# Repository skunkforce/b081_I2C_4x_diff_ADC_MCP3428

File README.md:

# edgy_board number b081
This design is part of the [edgy board project](https://github.com/skunkforce/edgy_boards).

# getting started
This repository uses submodules. After cloning use the command 

```$ git submodule update --init --recursive```

to pull the submodules before opening the project with kicad. 

# Tests
Tests can be found in [TESTS.md](TESTS.md)

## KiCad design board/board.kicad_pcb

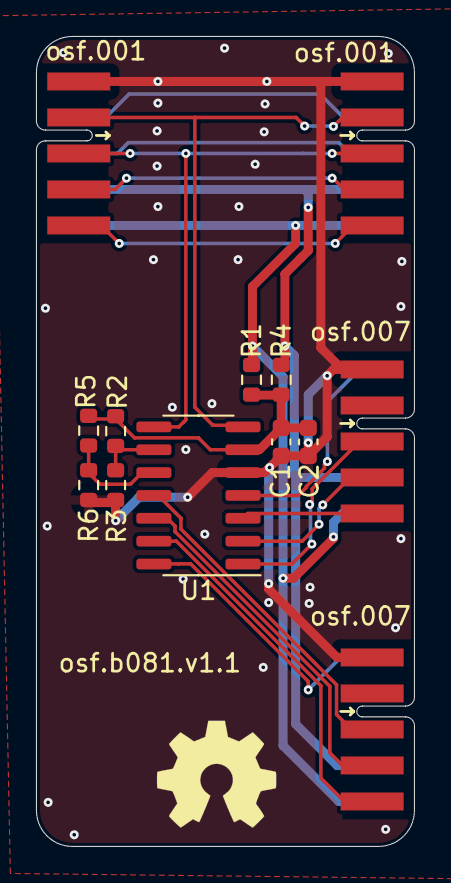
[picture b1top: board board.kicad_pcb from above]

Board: 2 copper layers, 21.0 x 45.0 mm, 14 parts (0 on the bottom side), 19 nets.

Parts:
C1: 100nF; C_0603_1608Metric
C2: 10uF; C_0603_1608Metric
J1: 001_I2C; on_edge_2x05_device
J2, J4: 007_ADC; on_edge_2x05_host
J3: 001_I2C; on_edge_2x05_host
LOGO1: Logo_Open_Hardware_Small; OSHW-Symbol_6.7x6mm_SilkScreen
R1, R3, R6: 0R; R_0603_1608Metric
R2, R4, R5: d.n.p; R_0603_1608Metric
U1: MCP3428; SOIC-14_3.9x8.7mm_P1.27mm

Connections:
/3.3V: J1.9 (3.3V), J2.9 (3.3V), J3.9 (3.3V), J4.9 (3.3V), R4.2
/5V: J1.10 (5V), J2.10 (5V), J3.10 (5V), J4.10 (5V), R1.2
/adc/AD0: R2.1, R3.1, U1.9 (Adr0)
/adc/AD1: R5.1, R6.2, U1.10 (Adr1)
/adc/AD1+: J4.3 (ADC0), U1.1 (CH1+)
/adc/AD1-: J4.4 (ADC1), U1.2 (CH1-)
/adc/AD2+: J4.5 (ADC2), U1.3 (CH2+)
/adc/AD2-: J4.6 (ADC3), U1.4 (CH2-)
/adc/AD3+: J2.3 (ADC0), U1.11 (CH3+)
/adc/AD3-: J2.4 (ADC1), U1.12 (CH3-)
/adc/AD4+: J2.5 (ADC2), U1.13 (CH4+)
/adc/AD4-: J2.6 (ADC3), U1.14 (CH4-)
/adc/SCL: J1.3 (SCL), J3.3 (SCL), U1.8 (SCL)
/adc/SDA: J1.2 (SDA), J3.2 (SDA), U1.7 (SDA)
/adc/VDD: C1.1, C2.1, R1.1, R2.2, R4.1, R5.2, U1.6 (VDD)
GND: C1.2, C2.2, J1.1 (GND), J2.1 (GND), J3.1 (GND), J4.1 (GND), R3.2, R6.1, U1.5 (VSS)
unnamed: J1.4 (CS/EN), J3.4 (CS/EN)
unnamed: J1.5 (INT), J3.5 (INT)
unnamed: J1.8 (~RESET), J3.8 (~RESET)

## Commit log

2023-02-27 initial
2023-02-27 initial README
2023-02-27 initial TESTS
2023-03-28 added copper pours and moved edgy specific components out of the subsheet
